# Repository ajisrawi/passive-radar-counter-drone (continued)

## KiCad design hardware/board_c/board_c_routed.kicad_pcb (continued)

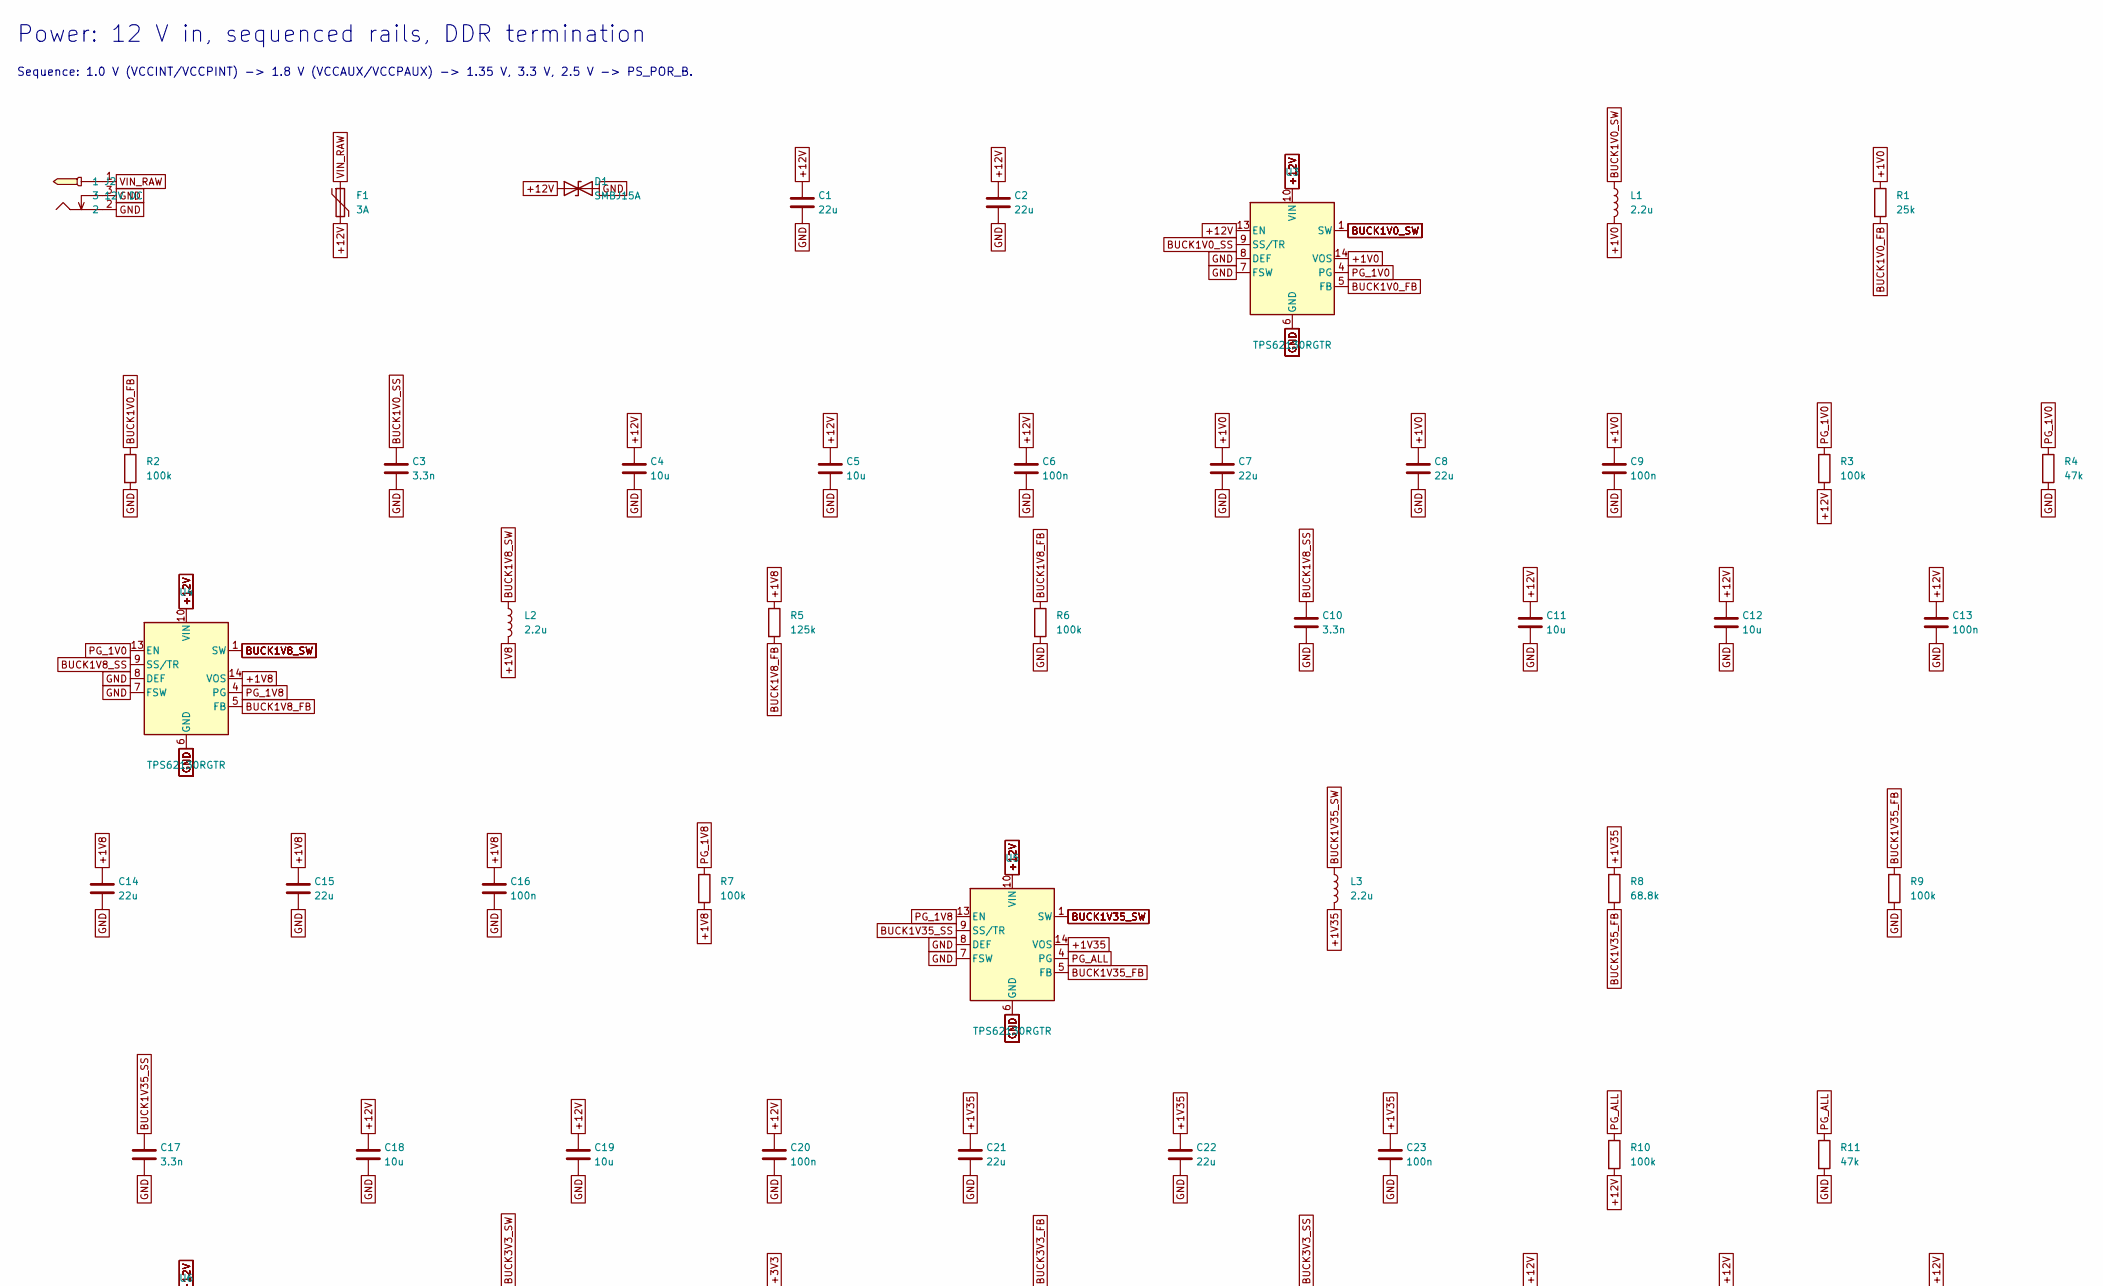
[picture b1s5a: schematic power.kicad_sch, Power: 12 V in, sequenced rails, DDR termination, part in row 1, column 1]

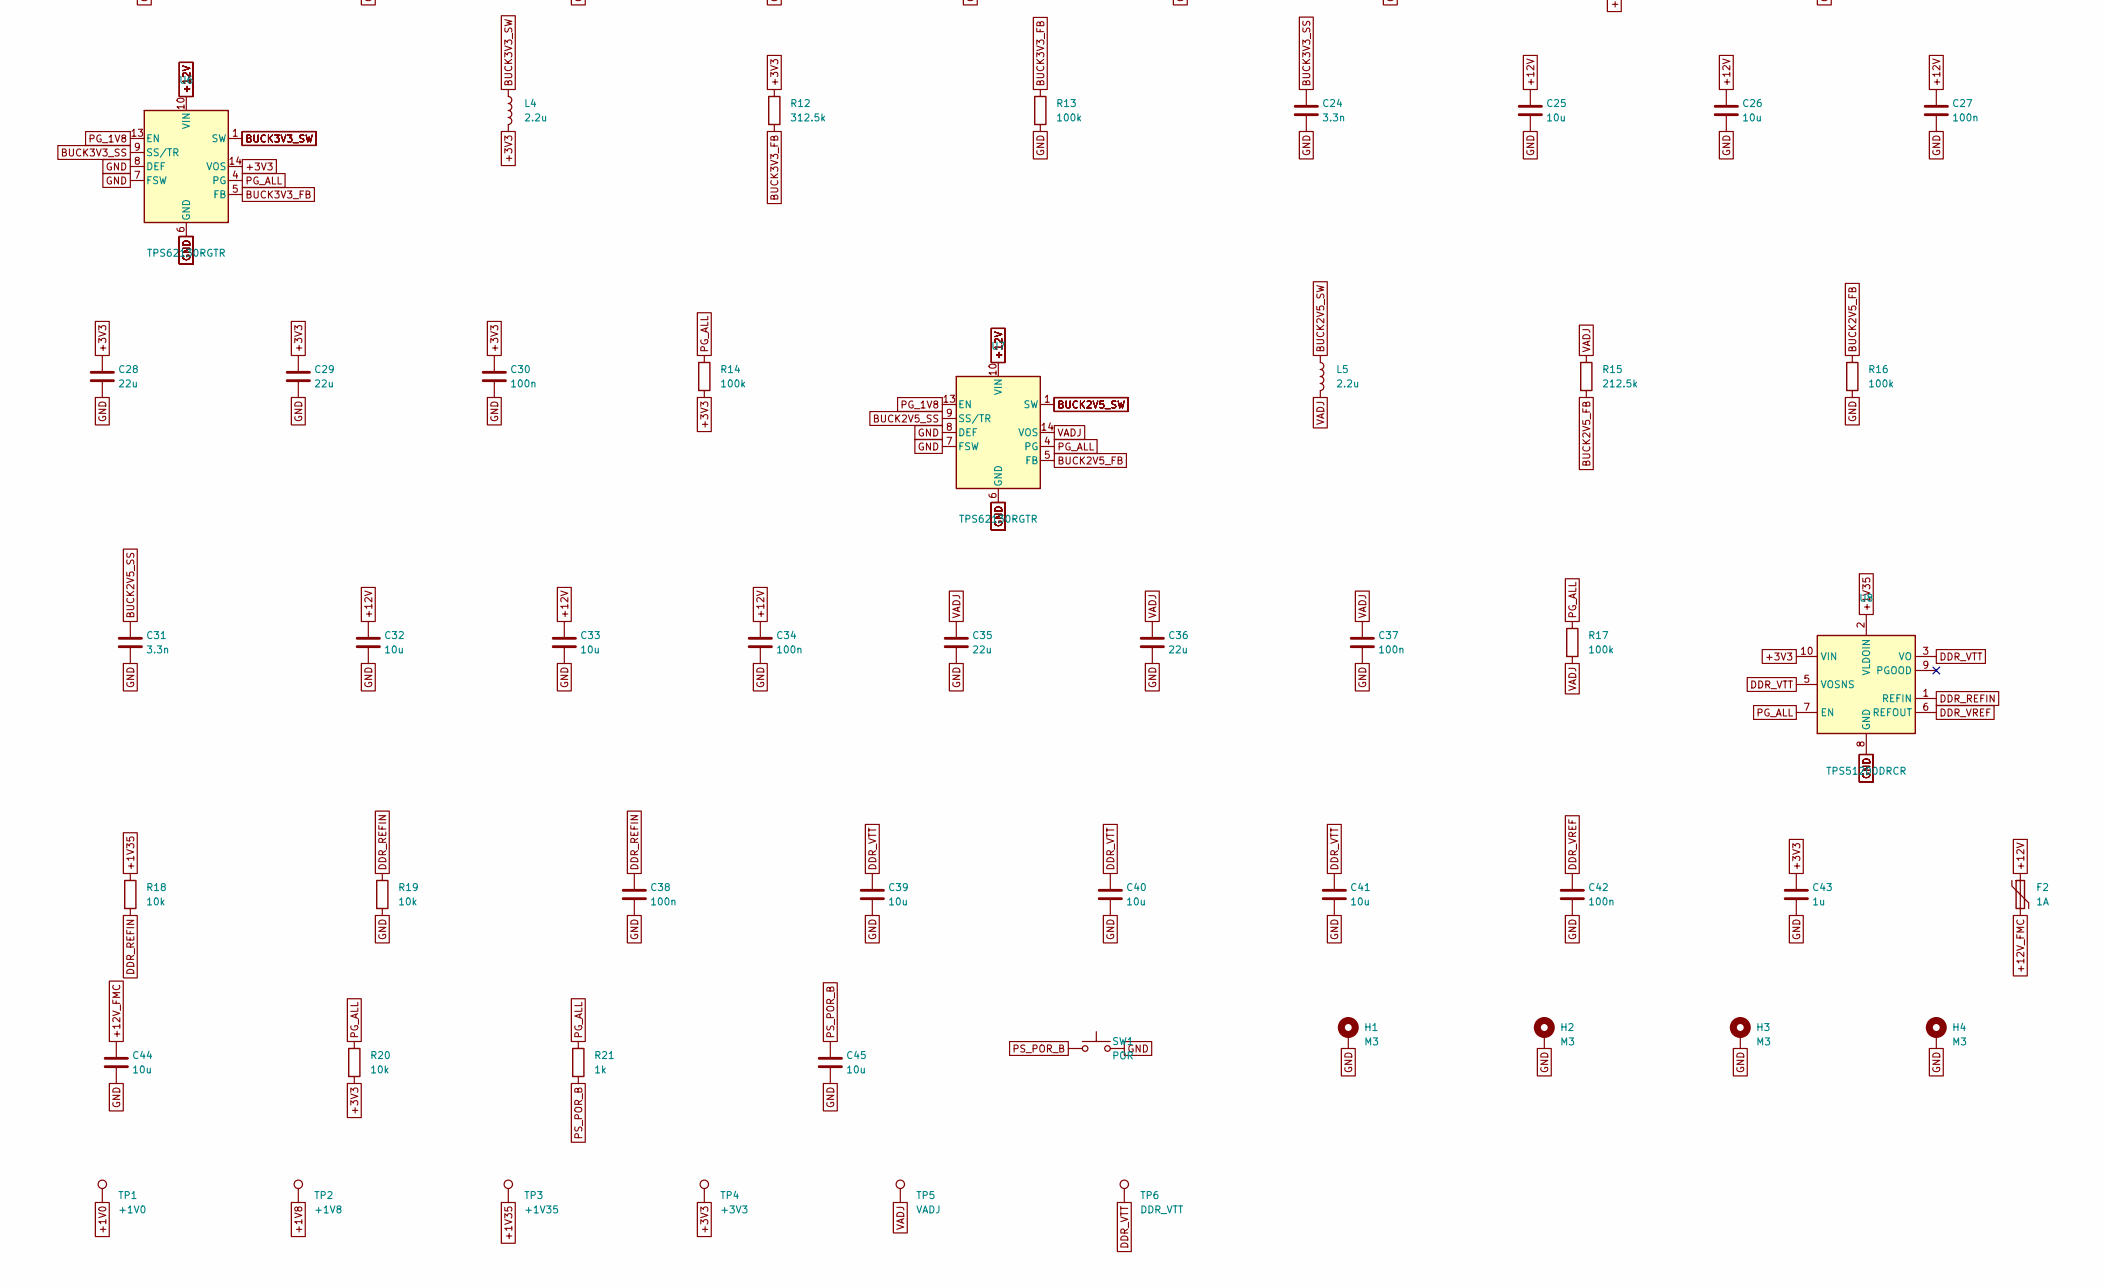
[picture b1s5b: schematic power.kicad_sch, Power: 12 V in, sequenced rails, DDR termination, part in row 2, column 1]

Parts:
C1, C2: 22u; C_1206_3216Metric
C3, C10, C17, C24, C31: 3.3n; C_0402_1005Metric
C4, C5, C11, C12, C18, C19, C25, C26, C32, C33, C44: 10u; C_0805_2012Metric
C6, C9, C13, C16, C20, C23, C27, C30, C34, C37, C38, C42: 100n; C_0402_1005Metric; LCSC C1525
C7, C8, C14, C15, C21, C22, C28, C29, C35, C36: 22u; C_0805_2012Metric; LCSC C45783
C39, C40, C41, C45: 10u; C_0603_1608Metric; LCSC C19702
C43: 1u; C_0402_1005Metric; LCSC C52923
D1: SMBJ15A; D_SMB
F1: 3A; Fuse_1206_3216Metric
F2: 1A; Fuse_1206_3216Metric
H1, H2, H3, H4: M3; MountingHole_3.2mm_M3_Pad_Via
J2: 12V DC; DC-IN-TH_DC-005C-20A; MPN DC-005C-20A; LCSC C84007
L1, L2, L3, L4, L5: 2.2u; L_Bourns-SRN4018; MPN SRN4018-2R2M
R1: 25k; R_0402_1005Metric
R2, R3, R6, R7, R9, R10, R13, R14, R16, R17: 100k; R_0402_1005Metric; LCSC C25741
R4, R11: 47k; R_0402_1005Metric
R5: 125k; R_0402_1005Metric
R8: 68.8k; R_0402_1005Metric
R12: 312.5k; R_0402_1005Metric
R15: 212.5k; R_0402_1005Metric
R18, R19: 10k; R_0402_1005Metric; Tolerance 1%; LCSC C25744
R20: 10k; R_0402_1005Metric; LCSC C25744
R21: 1k; R_0402_1005Metric; LCSC C11702
SW1: POR; SW_SPST_TL3342
TP1: +1V0; TestPoint_Pad_D1.0mm
TP2: +1V8; TestPoint_Pad_D1.0mm
TP3: +1V35; TestPoint_Pad_D1.0mm
TP4: +3V3; TestPoint_Pad_D1.0mm
TP5: VADJ; TestPoint_Pad_D1.0mm
TP6: DDR_VTT; TestPoint_Pad_D1.0mm
U3, U4, U5, U6, U7: TPS62130RGTR; VQFN-16-1EP_3x3mm_P0.5mm_EP1.68x1.68mm; MPN TPS62130RGTR; LCSC C43590
U8: TPS51200DRCR; VSON-10-1EP_3x3mm_P0.5mm_EP1.65x2.4mm; LCSC C34771

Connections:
+1V0: C7.1, C8.1, C9.1, L1.2, R1.1, TP1.1, U3.14 (VOS); also elsewhere on the board
+1V8: C14.1, C15.1, C16.1, L2.2, R5.1, R7.2, TP2.1, U4.14 (VOS); also elsewhere on the board
+1V35: C21.1, C22.1, C23.1, L3.2, R8.1, R18.1, TP3.1, U5.14 (VOS), U8.2 (VLDOIN); also elsewhere on the board
+3V3: C28.1, C29.1, C30.1, C43.1, L4.2, R12.1, R14.2, R20.2, TP4.1, U6.14 (VOS), U8.10 (VIN); also elsewhere on the board
+12V: C1.1, C2.1, C4.1, C5.1, C6.1, C11.1, C12.1, C13.1, C18.1, C19.1, C20.1, C25.1, C26.1, C27.1, C32.1, C33.1, C34.1, D1.1 (A1), F1.2, F2.1, R3.2, R10.2, U3.10 (VIN), U3.11 (VIN), U3.12 (VIN), U3.13 (EN), U4.10 (VIN), U4.11 (VIN), U4.12 (VIN), U5.10 (VIN), U5.11 (VIN), U5.12 (VIN), U6.10 (VIN), U6.11 (VIN), U6.12 (VIN), U7.10 (VIN), U7.11 (VIN), U7.12 (VIN)
+12V_FMC: C44.1, F2.2; also elsewhere on the board
BUCK1V0_FB: R1.2, R2.1, U3.5 (FB)
BUCK1V0_SS: C3.1, U3.9 (SS/TR)
BUCK1V0_SW: L1.1, U3.1 (SW), U3.2 (SW), U3.3 (SW)
BUCK1V8_FB: R5.2, R6.1, U4.5 (FB)
BUCK1V8_SS: C10.1, U4.9 (SS/TR)
BUCK1V8_SW: L2.1, U4.1 (SW), U4.2 (SW), U4.3 (SW)
BUCK1V35_FB: R8.2, R9.1, U5.5 (FB)
BUCK1V35_SS: C17.1, U5.9 (SS/TR)
BUCK1V35_SW: L3.1, U5.1 (SW), U5.2 (SW), U5.3 (SW)
BUCK2V5_FB: R15.2, R16.1, U7.5 (FB)
BUCK2V5_SS: C31.1, U7.9 (SS/TR)
BUCK2V5_SW: L5.1, U7.1 (SW), U7.2 (SW), U7.3 (SW)
BUCK3V3_FB: R12.2, R13.1, U6.5 (FB)
BUCK3V3_SS: C24.1, U6.9 (SS/TR)
BUCK3V3_SW: L4.1, U6.1 (SW), U6.2 (SW), U6.3 (SW)
DDR_REFIN: C38.1, R18.2, R19.1, U8.1 (REFIN)
DDR_VREF: C42.1, U8.6 (REFOUT); also elsewhere on the board
DDR_VTT: C39.1, C40.1, C41.1, TP6.1, U8.3 (VO), U8.5 (VOSNS); also elsewhere on the board
GND: C1.2, C2.2, C3.2, C4.2, C5.2, C6.2, C7.2, C8.2, C9.2, C10.2, C11.2, C12.2, C13.2, C14.2, C15.2, C16.2, C17.2, C18.2, C19.2, C20.2, C21.2, C22.2, C23.2, C24.2, C25.2, C26.2, C27.2, C28.2, C29.2, C30.2, C31.2, C32.2, C33.2, C34.2, C35.2, C36.2, C37.2, C38.2, C39.2, C40.2, C41.2, C42.2, C43.2, C44.2, C45.2, D1.2 (A2), H1.1, H2.1, H3.1, H4.1, J2.2, J2.3, R2.2, R4.2, R6.2, R9.2, R11.2, R13.2, R16.2, R19.2, SW1.2, U3.6 (GND), U3.7 (FSW), U3.8 (DEF), U3.15 (GND), U3.16 (GND), U3.17 (GND), U4.6 (GND), U4.7 (FSW), U4.8 (DEF), U4.15 (GND), U4.16 (GND), U4.17 (GND), U5.6 (GND), U5.7 (FSW), U5.8 (DEF), U5.15 (GND), U5.16 (GND), U5.17 (GND), U6.6 (GND), U6.7 (FSW), U6.8 (DEF), U6.15 (GND), U6.16 (GND), U6.17 (GND), U7.6 (GND), U7.7 (FSW), U7.8 (DEF), U7.15 (GND), U7.16 (GND), U7.17 (GND), U8.4 (GND), U8.8 (GND), U8.11 (GND); also elsewhere on the board
PG_1V0: R3.1, R4.1, U3.4 (PG), U4.13 (EN)
PG_1V8: R7.1, U4.4 (PG), U5.13 (EN), U6.13 (EN), U7.13 (EN)
PG_ALL: R10.1, R11.1, R14.1, R17.1, R20.1, R21.1, U5.4 (PG), U6.4 (PG), U7.4 (PG), U8.7 (EN); also elsewhere on the board
PS_POR_B: C45.1, R21.2, SW1.1; also elsewhere on the board
VADJ: C35.1, C36.1, C37.1, L5.2, R15.1, R17.2, TP5.1, U7.14 (VOS); also elsewhere on the board
VIN_RAW: F1.1, J2.1

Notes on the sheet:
Power: 12 V in, sequenced rails, DDR termination
Sequence: 1.0 V (VCCINT/VCCPINT) -> 1.8 V (VCCAUX/VCCPAUX) -> 1.35 V, 3.3 V, 2.5 V -> PS_POR_B.

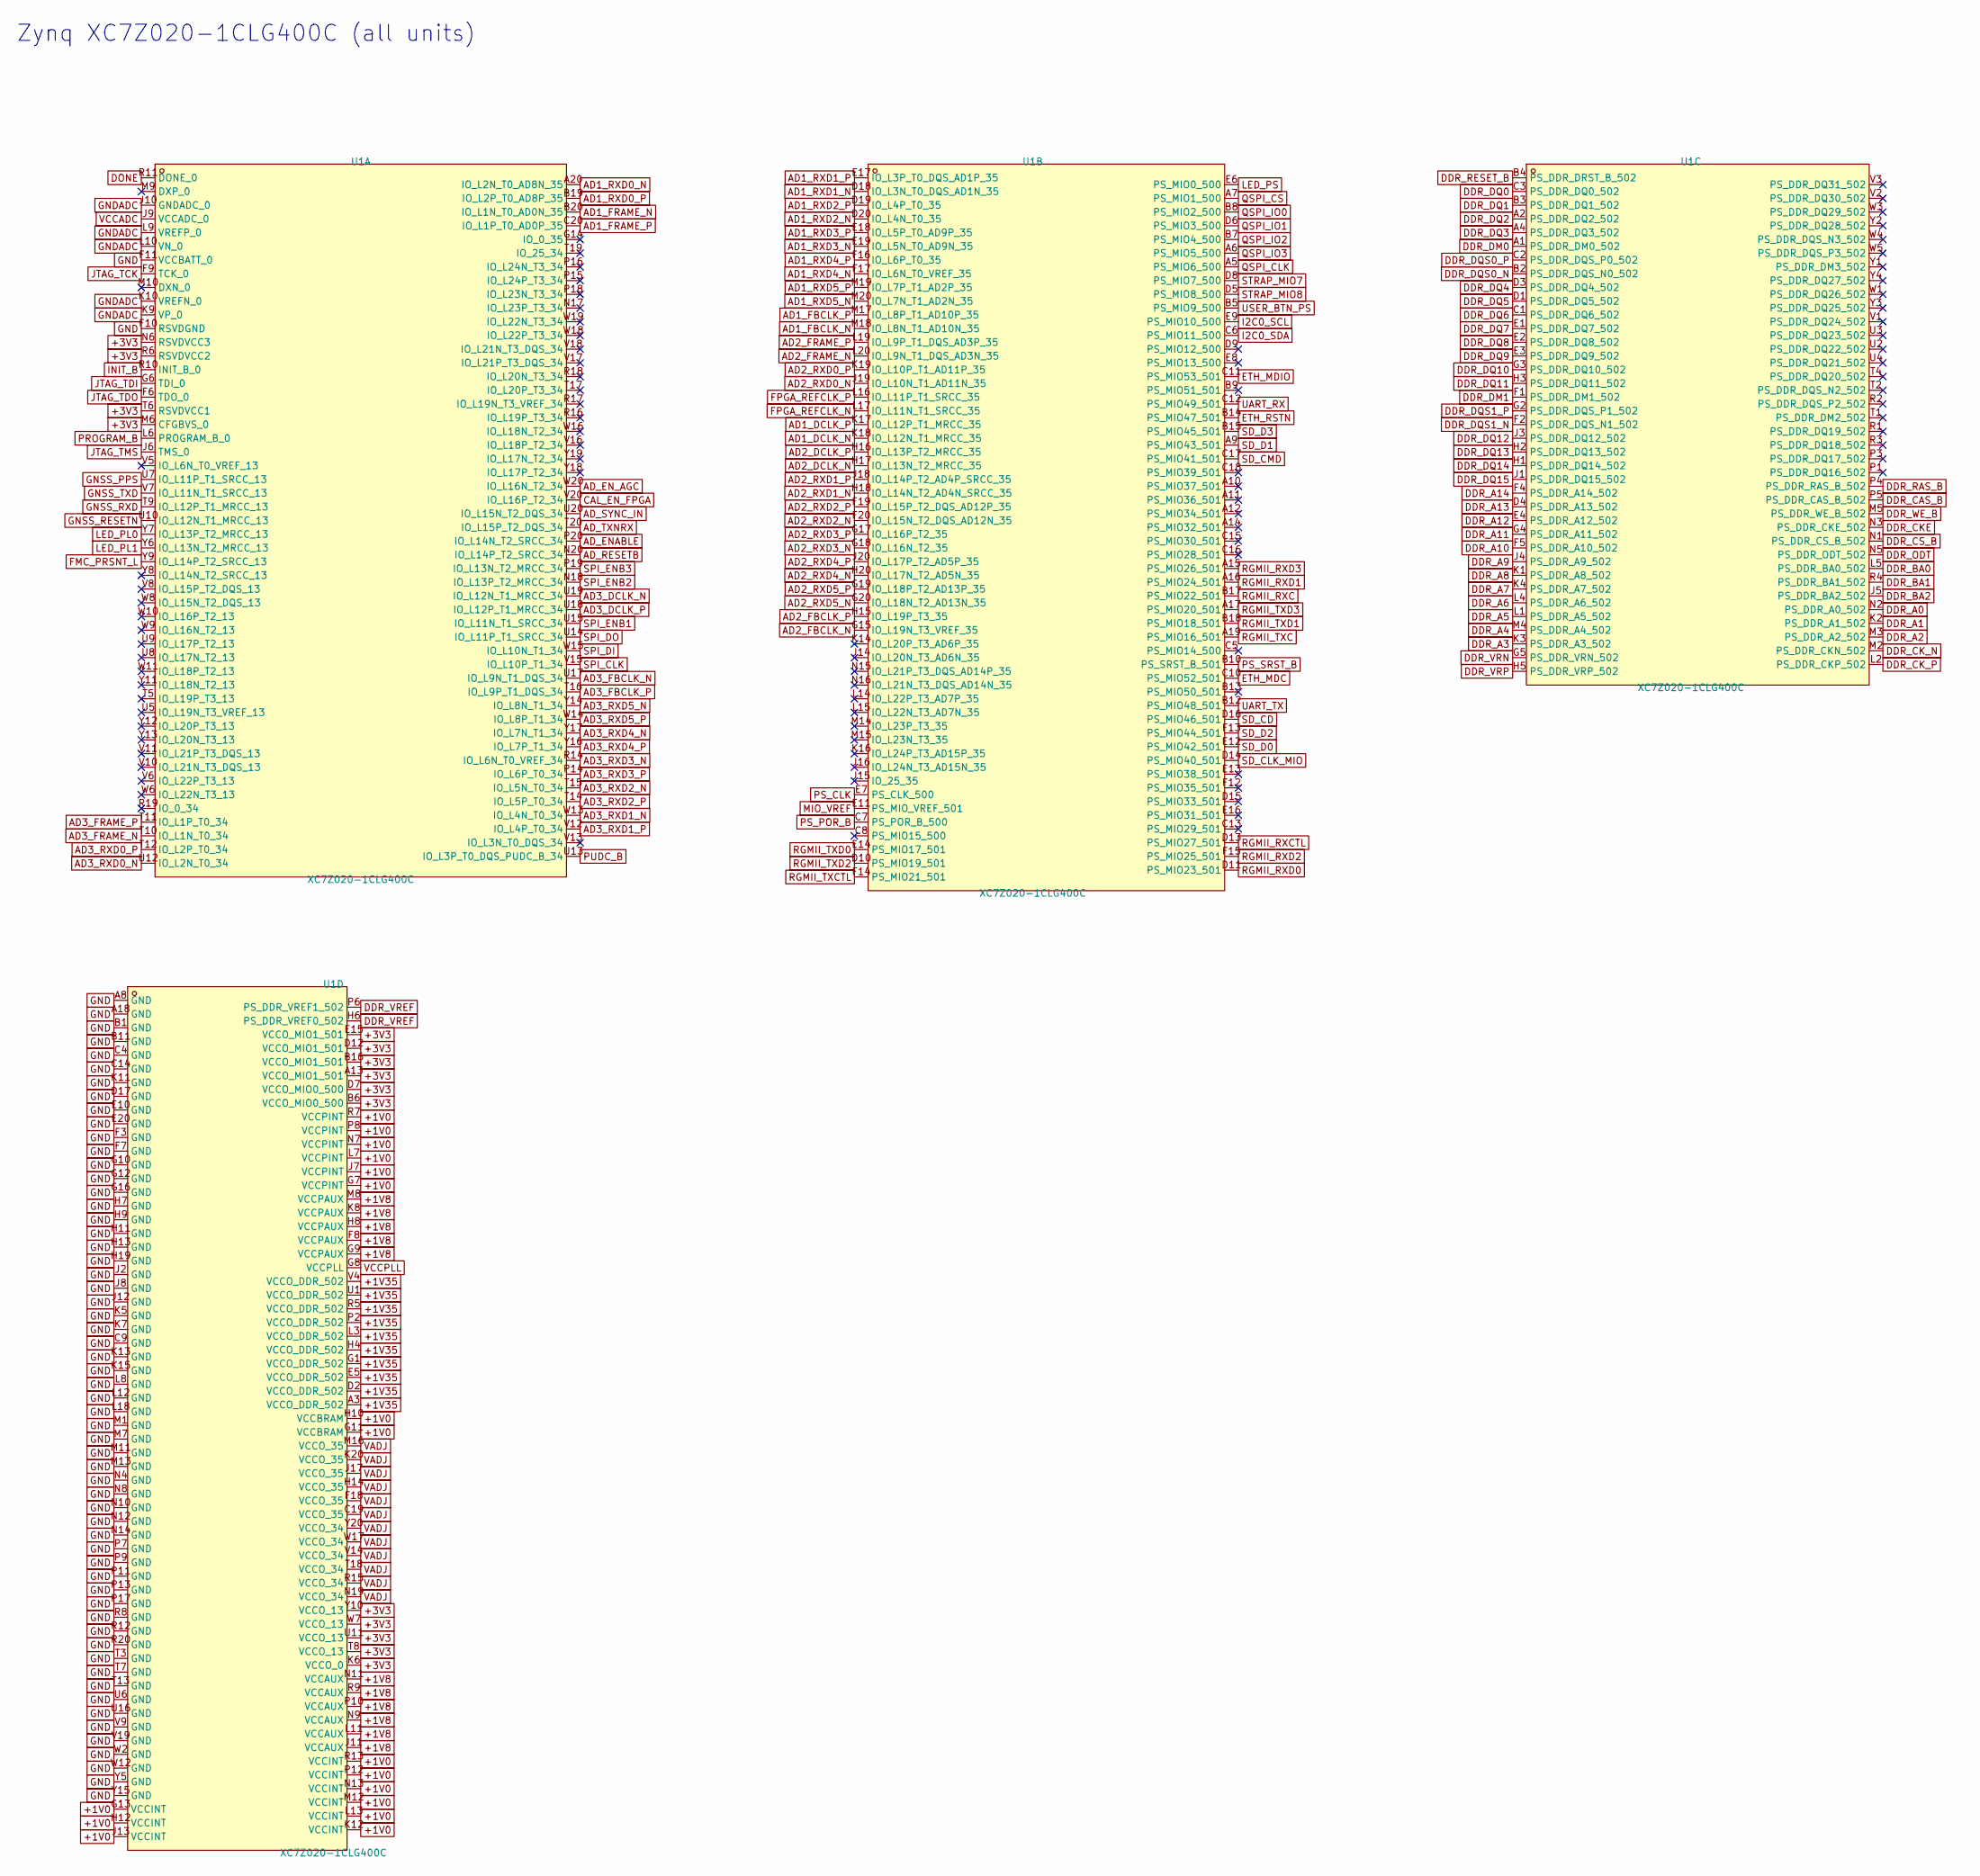
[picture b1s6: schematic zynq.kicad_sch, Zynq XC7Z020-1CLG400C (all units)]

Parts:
U1: XC7Z020-1CLG400C; FBGA-400_L17.0-W17.0-R20-C20-P0.80-TL; MPN XC7Z020-1CLG400C; LCSC C2988113

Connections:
+1V0: U1.G7 (VCCPINT), U1.G11 (VCCBRAM), U1.G13 (VCCINT), U1.H10 (VCCBRAM), U1.H12 (VCCINT), U1.J7 (VCCPINT), U1.J13 (VCCINT), U1.K12 (VCCINT), U1.L7 (VCCPINT), U1.L13 (VCCINT), U1.M12 (VCCINT), U1.N7 (VCCPINT), U1.N13 (VCCINT), U1.P8 (VCCPINT), U1.P12 (VCCINT), U1.R7 (VCCPINT), U1.R13 (VCCINT); also elsewhere on the board
+1V8: U1.F8 (VCCPAUX), U1.G9 (VCCPAUX), U1.H8 (VCCPAUX), U1.J11 (VCCAUX), U1.K8 (VCCPAUX), U1.L11 (VCCAUX), U1.M8 (VCCPAUX), U1.N9 (VCCAUX), U1.N11 (VCCAUX), U1.P10 (VCCAUX), U1.R9 (VCCAUX); also elsewhere on the board
+1V35: U1.A3 (VCCO_DDR_502), U1.D2 (VCCO_DDR_502), U1.E5 (VCCO_DDR_502), U1.G1 (VCCO_DDR_502), U1.H4 (VCCO_DDR_502), U1.L3 (VCCO_DDR_502), U1.P2 (VCCO_DDR_502), U1.R5 (VCCO_DDR_502), U1.U1 (VCCO_DDR_502), U1.V4 (VCCO_DDR_502); also elsewhere on the board
+3V3: U1.A13 (VCCO_MIO1_501), U1.B6 (VCCO_MIO0_500), U1.B16 (VCCO_MIO1_501), U1.D7 (VCCO_MIO0_500), U1.D12 (VCCO_MIO1_501), U1.E15 (VCCO_MIO1_501), U1.K6 (VCCO_0), U1.M6 (CFGBVS_0), U1.N6 (RSVDVCC3), U1.R6 (RSVDVCC2), U1.T6 (RSVDVCC1), U1.T8 (VCCO_13), U1.U11 (VCCO_13), U1.W7 (VCCO_13), U1.Y10 (VCCO_13); also elsewhere on the board
AD1_DCLK_N: U1.K18 (IO_L12N_T1_MRCC_35); also elsewhere on the board
AD1_DCLK_P: U1.K17 (IO_L12P_T1_MRCC_35); also elsewhere on the board
AD1_FBCLK_N: U1.M18 (IO_L8N_T1_AD10N_35); also elsewhere on the board
AD1_FBCLK_P: U1.M17 (IO_L8P_T1_AD10P_35); also elsewhere on the board
AD1_FRAME_N: U1.B20 (IO_L1N_T0_AD0N_35); also elsewhere on the board
AD1_FRAME_P: U1.C20 (IO_L1P_T0_AD0P_35); also elsewhere on the board
AD1_RXD0_N: U1.A20 (IO_L2N_T0_AD8N_35); also elsewhere on the board
AD1_RXD0_P: U1.B19 (IO_L2P_T0_AD8P_35); also elsewhere on the board
AD1_RXD1_N: U1.D18 (IO_L3N_T0_DQS_AD1N_35); also elsewhere on the board
AD1_RXD1_P: U1.E17 (IO_L3P_T0_DQS_AD1P_35); also elsewhere on the board
AD1_RXD2_N: U1.D20 (IO_L4N_T0_35); also elsewhere on the board
AD1_RXD2_P: U1.D19 (IO_L4P_T0_35); also elsewhere on the board
AD1_RXD3_N: U1.E19 (IO_L5N_T0_AD9N_35); also elsewhere on the board
AD1_RXD3_P: U1.E18 (IO_L5P_T0_AD9P_35); also elsewhere on the board
AD1_RXD4_N: U1.F17 (IO_L6N_T0_VREF_35); also elsewhere on the board
AD1_RXD4_P: U1.F16 (IO_L6P_T0_35); also elsewhere on the board
AD1_RXD5_N: U1.M20 (IO_L7N_T1_AD2N_35); also elsewhere on the board
AD1_RXD5_P: U1.M19 (IO_L7P_T1_AD2P_35); also elsewhere on the board
AD2_DCLK_N: U1.H17 (IO_L13N_T2_MRCC_35); also elsewhere on the board
AD2_DCLK_P: U1.H16 (IO_L13P_T2_MRCC_35); also elsewhere on the board
AD2_FBCLK_N: U1.G15 (IO_L19N_T3_VREF_35); also elsewhere on the board
AD2_FBCLK_P: U1.H15 (IO_L19P_T3_35); also elsewhere on the board
AD2_FRAME_N: U1.L20 (IO_L9N_T1_DQS_AD3N_35); also elsewhere on the board
AD2_FRAME_P: U1.L19 (IO_L9P_T1_DQS_AD3P_35); also elsewhere on the board
AD2_RXD0_N: U1.J19 (IO_L10N_T1_AD11N_35); also elsewhere on the board
AD2_RXD0_P: U1.K19 (IO_L10P_T1_AD11P_35); also elsewhere on the board
AD2_RXD1_N: U1.H18 (IO_L14N_T2_AD4N_SRCC_35); also elsewhere on the board
AD2_RXD1_P: U1.J18 (IO_L14P_T2_AD4P_SRCC_35); also elsewhere on the board
AD2_RXD2_N: U1.F20 (IO_L15N_T2_DQS_AD12N_35); also elsewhere on the board
AD2_RXD2_P: U1.F19 (IO_L15P_T2_DQS_AD12P_35); also elsewhere on the board
AD2_RXD3_N: U1.G18 (IO_L16N_T2_35); also elsewhere on the board
AD2_RXD3_P: U1.G17 (IO_L16P_T2_35); also elsewhere on the board
AD2_RXD4_N: U1.H20 (IO_L17N_T2_AD5N_35); also elsewhere on the board
AD2_RXD4_P: U1.J20 (IO_L17P_T2_AD5P_35); also elsewhere on the board
AD2_RXD5_N: U1.G20 (IO_L18N_T2_AD13N_35); also elsewhere on the board
AD2_RXD5_P: U1.G19 (IO_L18P_T2_AD13P_35); also elsewhere on the board
AD3_DCLK_N: U1.U19 (IO_L12N_T1_MRCC_34); also elsewhere on the board
AD3_DCLK_P: U1.U18 (IO_L12P_T1_MRCC_34); also elsewhere on the board
AD3_FBCLK_N: U1.U17 (IO_L9N_T1_DQS_34); also elsewhere on the board
AD3_FBCLK_P: U1.T16 (IO_L9P_T1_DQS_34); also elsewhere on the board
AD3_FRAME_N: U1.T10 (IO_L1N_T0_34); also elsewhere on the board
AD3_FRAME_P: U1.T11 (IO_L1P_T0_34); also elsewhere on the board
AD3_RXD0_N: U1.U12 (IO_L2N_T0_34); also elsewhere on the board
AD3_RXD0_P: U1.T12 (IO_L2P_T0_34); also elsewhere on the board
AD3_RXD1_N: U1.W13 (IO_L4N_T0_34); also elsewhere on the board
AD3_RXD1_P: U1.V12 (IO_L4P_T0_34); also elsewhere on the board
AD3_RXD2_N: U1.T15 (IO_L5N_T0_34); also elsewhere on the board
AD3_RXD2_P: U1.T14 (IO_L5P_T0_34); also elsewhere on the board
AD3_RXD3_N: U1.R14 (IO_L6N_T0_VREF_34); also elsewhere on the board
AD3_RXD3_P: U1.P14 (IO_L6P_T0_34); also elsewhere on the board
AD3_RXD4_N: U1.Y17 (IO_L7N_T1_34); also elsewhere on the board
AD3_RXD4_P: U1.Y16 (IO_L7P_T1_34); also elsewhere on the board
AD3_RXD5_N: U1.Y14 (IO_L8N_T1_34); also elsewhere on the board
AD3_RXD5_P: U1.W14 (IO_L8P_T1_34); also elsewhere on the board
AD_ENABLE: U1.P20 (IO_L14N_T2_SRCC_34); also elsewhere on the board
AD_EN_AGC: U1.W20 (IO_L16N_T2_34); also elsewhere on the board
AD_RESETB: U1.N20 (IO_L14P_T2_SRCC_34); also elsewhere on the board
AD_SYNC_IN: U1.U20 (IO_L15N_T2_DQS_34); also elsewhere on the board
AD_TXNRX: U1.T20 (IO_L15P_T2_DQS_34); also elsewhere on the board
CAL_EN_FPGA: U1.V20 (IO_L16P_T2_34); also elsewhere on the board
DDR_A0: U1.N2 (PS_DDR_A0_502); also elsewhere on the board
DDR_A1: U1.K2 (PS_DDR_A1_502); also elsewhere on the board
DDR_A2: U1.M3 (PS_DDR_A2_502); also elsewhere on the board
DDR_A3: U1.K3 (PS_DDR_A3_502); also elsewhere on the board
DDR_A4: U1.M4 (PS_DDR_A4_502); also elsewhere on the board
DDR_A5: U1.L1 (PS_DDR_A5_502); also elsewhere on the board
DDR_A6: U1.L4 (PS_DDR_A6_502); also elsewhere on the board
DDR_A7: U1.K4 (PS_DDR_A7_502); also elsewhere on the board
DDR_A8: U1.K1 (PS_DDR_A8_502); also elsewhere on the board
DDR_A9: U1.J4 (PS_DDR_A9_502); also elsewhere on the board
DDR_A10: U1.F5 (PS_DDR_A10_502); also elsewhere on the board
DDR_A11: U1.G4 (PS_DDR_A11_502); also elsewhere on the board
DDR_A12: U1.E4 (PS_DDR_A12_502); also elsewhere on the board
DDR_A13: U1.D4 (PS_DDR_A13_502); also elsewhere on the board
DDR_A14: U1.F4 (PS_DDR_A14_502); also elsewhere on the board
DDR_BA0: U1.L5 (PS_DDR_BA0_502); also elsewhere on the board
DDR_BA1: U1.R4 (PS_DDR_BA1_502); also elsewhere on the board
DDR_BA2: U1.J5 (PS_DDR_BA2_502); also elsewhere on the board
DDR_CAS_B: U1.P5 (PS_DDR_CAS_B_502); also elsewhere on the board
DDR_CKE: U1.N3 (PS_DDR_CKE_502); also elsewhere on the board
DDR_CK_N: U1.M2 (PS_DDR_CKN_502); also elsewhere on the board
DDR_CK_P: U1.L2 (PS_DDR_CKP_502); also elsewhere on the board
DDR_CS_B: U1.N1 (PS_DDR_CS_B_502); also elsewhere on the board
DDR_DM0: U1.A1 (PS_DDR_DM0_502); also elsewhere on the board
DDR_DM1: U1.F1 (PS_DDR_DM1_502); also elsewhere on the board
DDR_DQ0: U1.C3 (PS_DDR_DQ0_502); also elsewhere on the board
DDR_DQ1: U1.B3 (PS_DDR_DQ1_502); also elsewhere on the board
DDR_DQ2: U1.A2 (PS_DDR_DQ2_502); also elsewhere on the board
DDR_DQ3: U1.A4 (PS_DDR_DQ3_502); also elsewhere on the board
DDR_DQ4: U1.D3 (PS_DDR_DQ4_502); also elsewhere on the board
DDR_DQ5: U1.D1 (PS_DDR_DQ5_502); also elsewhere on the board
DDR_DQ6: U1.C1 (PS_DDR_DQ6_502); also elsewhere on the board
DDR_DQ7: U1.E1 (PS_DDR_DQ7_502); also elsewhere on the board
DDR_DQ8: U1.E2 (PS_DDR_DQ8_502); also elsewhere on the board
DDR_DQ9: U1.E3 (PS_DDR_DQ9_502); also elsewhere on the board
DDR_DQ10: U1.G3 (PS_DDR_DQ10_502); also elsewhere on the board
DDR_DQ11: U1.H3 (PS_DDR_DQ11_502); also elsewhere on the board
DDR_DQ12: U1.J3 (PS_DDR_DQ12_502); also elsewhere on the board
DDR_DQ13: U1.H2 (PS_DDR_DQ13_502); also elsewhere on the board
DDR_DQ14: U1.H1 (PS_DDR_DQ14_502); also elsewhere on the board
DDR_DQ15: U1.J1 (PS_DDR_DQ15_502); also elsewhere on the board
DDR_DQS0_N: U1.B2 (PS_DDR_DQS_N0_502); also elsewhere on the board
DDR_DQS0_P: U1.C2 (PS_DDR_DQS_P0_502); also elsewhere on the board
DDR_DQS1_N: U1.F2 (PS_DDR_DQS_N1_502); also elsewhere on the board
DDR_DQS1_P: U1.G2 (PS_DDR_DQS_P1_502); also elsewhere on the board
DDR_ODT: U1.N5 (PS_DDR_ODT_502); also elsewhere on the board
DDR_RAS_B: U1.P4 (PS_DDR_RAS_B_502); also elsewhere on the board
DDR_RESET_B: U1.B4 (PS_DDR_DRST_B_502); also elsewhere on the board
DDR_VREF: U1.H6 (PS_DDR_VREF0_502), U1.P6 (PS_DDR_VREF1_502); also elsewhere on the board
DDR_VRN: U1.G5 (PS_DDR_VRN_502); also elsewhere on the board
DDR_VRP: U1.H5 (PS_DDR_VRP_502); also elsewhere on the board
DDR_WE_B: U1.M5 (PS_DDR_WE_B_502); also elsewhere on the board
DONE: U1.R11 (DONE_0); also elsewhere on the board
ETH_MDC: U1.C10 (PS_MIO52_501); also elsewhere on the board
ETH_MDIO: U1.C11 (PS_MIO53_501); also elsewhere on the board
ETH_RSTN: U1.B14 (PS_MIO47_501); also elsewhere on the board
FMC_PRSNT_L: U1.Y9 (IO_L14P_T2_SRCC_13); also elsewhere on the board
FPGA_REFCLK_N: U1.L17 (IO_L11N_T1_SRCC_35); also elsewhere on the board
FPGA_REFCLK_P: U1.L16 (IO_L11P_T1_SRCC_35); also elsewhere on the board
GND: U1.A8 (GND), U1.A18 (GND), U1.B1 (GND), U1.B11 (GND), U1.C4 (GND), U1.C9 (GND), U1.C14 (GND), U1.D17 (GND), U1.E10 (GND), U1.E20 (GND), U1.F3 (GND), U1.F7 (GND), U1.F10 (RSVDGND), U1.F11 (VCCBATT_0), U1.G10 (GND), U1.G12 (GND), U1.G16 (GND), U1.H7 (GND), U1.H9 (GND), U1.H11 (GND), U1.H13 (GND), U1.H19 (GND), U1.J2 (GND), U1.J8 (GND), U1.J12 (GND), U1.K5 (GND), U1.K7 (GND), U1.K11 (GND), U1.K13 (GND), U1.K15 (GND), U1.L8 (GND), U1.L12 (GND), U1.L18 (GND), U1.M1 (GND), U1.M7 (GND), U1.M11 (GND), U1.M13 (GND), U1.N4 (GND), U1.N8 (GND), U1.N10 (GND), U1.N12 (GND), U1.N14 (GND), U1.P7 (GND), U1.P9 (GND), U1.P11 (GND), U1.P13 (GND), U1.P17 (GND), U1.R8 (GND), U1.R12 (GND), U1.R20 (GND), U1.T3 (GND), U1.T7 (GND), U1.T13 (GND), U1.U6 (GND), U1.U16 (GND), U1.V9 (GND), U1.V19 (GND), U1.W2 (GND), U1.W12 (GND), U1.Y5 (GND), U1.Y15 (GND); also elsewhere on the board
GNDADC: U1.J10 (GNDADC_0), U1.K9 (VP_0), U1.K10 (VREFN_0), U1.L9 (VREFP_0), U1.L10 (VN_0); also elsewhere on the board
GNSS_PPS: U1.U7 (IO_L11P_T1_SRCC_13); also elsewhere on the board
GNSS_RESETN: U1.U10 (IO_L12N_T1_MRCC_13); also elsewhere on the board
GNSS_RXD: U1.T9 (IO_L12P_T1_MRCC_13); also elsewhere on the board
GNSS_TXD: U1.V7 (IO_L11N_T1_SRCC_13); also elsewhere on the board
I2C0_SCL: U1.E9 (PS_MIO10_500); also elsewhere on the board
I2C0_SDA: U1.C6 (PS_MIO11_500); also elsewhere on the board
INIT_B: U1.R10 (INIT_B_0); also elsewhere on the board
JTAG_TCK: U1.F9 (TCK_0); also elsewhere on the board
JTAG_TDI: U1.G6 (TDI_0); also elsewhere on the board
JTAG_TDO: U1.F6 (TDO_0); also elsewhere on the board
JTAG_TMS: U1.J6 (TMS_0); also elsewhere on the board
LED_PL0: U1.Y7 (IO_L13P_T2_MRCC_13); also elsewhere on the board
LED_PL1: U1.Y6 (IO_L13N_T2_MRCC_13); also elsewhere on the board
LED_PS: U1.E6 (PS_MIO0_500); also elsewhere on the board
MIO_VREF: U1.E11 (PS_MIO_VREF_501); also elsewhere on the board
PROGRAM_B: U1.L6 (PROGRAM_B_0); also elsewhere on the board
PS_CLK: U1.E7 (PS_CLK_500); also elsewhere on the board
PS_POR_B: U1.C7 (PS_POR_B_500); also elsewhere on the board
PS_SRST_B: U1.B10 (PS_SRST_B_501); also elsewhere on the board
PUDC_B: U1.U13 (IO_L3P_T0_DQS_PUDC_B_34); also elsewhere on the board
QSPI_CLK: U1.A5 (PS_MIO6_500); also elsewhere on the board
QSPI_CS: U1.A7 (PS_MIO1_500); also elsewhere on the board
QSPI_IO0: U1.B8 (PS_MIO2_500); also elsewhere on the board
QSPI_IO1: U1.D6 (PS_MIO3_500); also elsewhere on the board
QSPI_IO2: U1.B7 (PS_MIO4_500); also elsewhere on the board
QSPI_IO3: U1.A6 (PS_MIO5_500); also elsewhere on the board
RGMII_RXC: U1.B17 (PS_MIO22_501); also elsewhere on the board
RGMII_RXCTL: U1.D13 (PS_MIO27_501); also elsewhere on the board
RGMII_RXD0: U1.D11 (PS_MIO23_501); also elsewhere on the board
RGMII_RXD1: U1.A16 (PS_MIO24_501); also elsewhere on the board
RGMII_RXD2: U1.F15 (PS_MIO25_501); also elsewhere on the board
RGMII_RXD3: U1.A15 (PS_MIO26_501); also elsewhere on the board
RGMII_TXC: U1.A19 (PS_MIO16_501); also elsewhere on the board
RGMII_TXCTL: U1.F14 (PS_MIO21_501); also elsewhere on the board
RGMII_TXD0: U1.E14 (PS_MIO17_501); also elsewhere on the board
RGMII_TXD1: U1.B18 (PS_MIO18_501); also elsewhere on the board
RGMII_TXD2: U1.D10 (PS_MIO19_501); also elsewhere on the board
RGMII_TXD3: U1.A17 (PS_MIO20_501); also elsewhere on the board
SD_CD: U1.D16 (PS_MIO46_501); also elsewhere on the board
SD_CLK_MIO: U1.D14 (PS_MIO40_501); also elsewhere on the board
SD_CMD: U1.C17 (PS_MIO41_501); also elsewhere on the board
SD_D0: U1.E12 (PS_MIO42_501); also elsewhere on the board
SD_D1: U1.A9 (PS_MIO43_501); also elsewhere on the board
SD_D2: U1.F13 (PS_MIO44_501); also elsewhere on the board
SD_D3: U1.B15 (PS_MIO45_501); also elsewhere on the board
SPI_CLK: U1.V15 (IO_L10P_T1_34); also elsewhere on the board
SPI_DI: U1.W15 (IO_L10N_T1_34); also elsewhere on the board
SPI_DO: U1.U14 (IO_L11P_T1_SRCC_34); also elsewhere on the board
SPI_ENB1: U1.U15 (IO_L11N_T1_SRCC_34); also elsewhere on the board
SPI_ENB2: U1.N18 (IO_L13P_T2_MRCC_34); also elsewhere on the board
SPI_ENB3: U1.P19 (IO_L13N_T2_MRCC_34); also elsewhere on the board
STRAP_MIO7: U1.D8 (PS_MIO7_500); also elsewhere on the board
STRAP_MIO8: U1.D5 (PS_MIO8_500); also elsewhere on the board
UART_RX: U1.C12 (PS_MIO49_501); also elsewhere on the board
UART_TX: U1.B12 (PS_MIO48_501); also elsewhere on the board
USER_BTN_PS: U1.B5 (PS_MIO9_500); also elsewhere on the board
VADJ: U1.C19 (VCCO_35), U1.F18 (VCCO_35), U1.H14 (VCCO_35), U1.J17 (VCCO_35), U1.K20 (VCCO_35), U1.M16 (VCCO_35), U1.N19 (VCCO_34), U1.R15 (VCCO_34), U1.T18 (VCCO_34), U1.V14 (VCCO_34), U1.W17 (VCCO_34), U1.Y20 (VCCO_34); also elsewhere on the board
VCCADC: U1.J9 (VCCADC_0); also elsewhere on the board
VCCPLL: U1.G8 (VCCPLL); also elsewhere on the board

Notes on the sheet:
Zynq XC7Z020-1CLG400C (all units)
